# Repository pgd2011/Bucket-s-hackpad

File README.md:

# Bucket's Hackpad: RP2040 Macro Keyboard ⌨️

A custom macro pad project utilizing the Seeed XIAO RP2040 microcontroller for USB input and RGB lighting.

Built as part of [Hack Club](https://hackclub.com)'s Blueprint program.

---

## ✨ Features
*   **Microcontroller:** Seeed XIAO RP2040 (motherboard of the keyboard)
*   **Switches:** MX-Style switches (Note: the project documentation lists 16 components used, despite the description mentioning 6 keys)
*   **Lighting:** SK6812 MINI-E LEDs (RGB lighting for the keyboard)
*   **Design Tools:** Schematic & PCB designed using **KiCad**; Case designed using **Autodesk Fusion**

## 🛠️ Bill of Materials (BOM)
| Item | Quantity | Description |
| :--- | :---: | :--- |
| Seeed XIAO RP2040 | x1 | Main motherboard |
| MX-Style switches | x16 | The keys of the keyboard |
| SK6812 MINI-E LEDs | x2 | RGB lighting |
| M3x16mm screws | x4 | For joining the top and bottom of the case |
| 3D Printed Case | x1 | Custom enclosure |

| Case Enclosure | PCB Layout | Circuit Schematic |
| :---: | :---: | :---: |
|  |  |  |

## 💡 How It Was Made
The project was created by wiring the switches in a matrix and routing the PCB in KiCad. The mechanical enclosure design took some effort to finalize the exact dimensions in Fusion 360.

## 😄 Acknowledgment
*   This project wouldn't have been possible without the documentation from HackClub themselves from https://blueprint.hackclub.com/hackpad
*   My sincere thanks to my elder brother [@P-G-D](https://github.com/P-G-D) for guidance, motivation, and helpful conversations.

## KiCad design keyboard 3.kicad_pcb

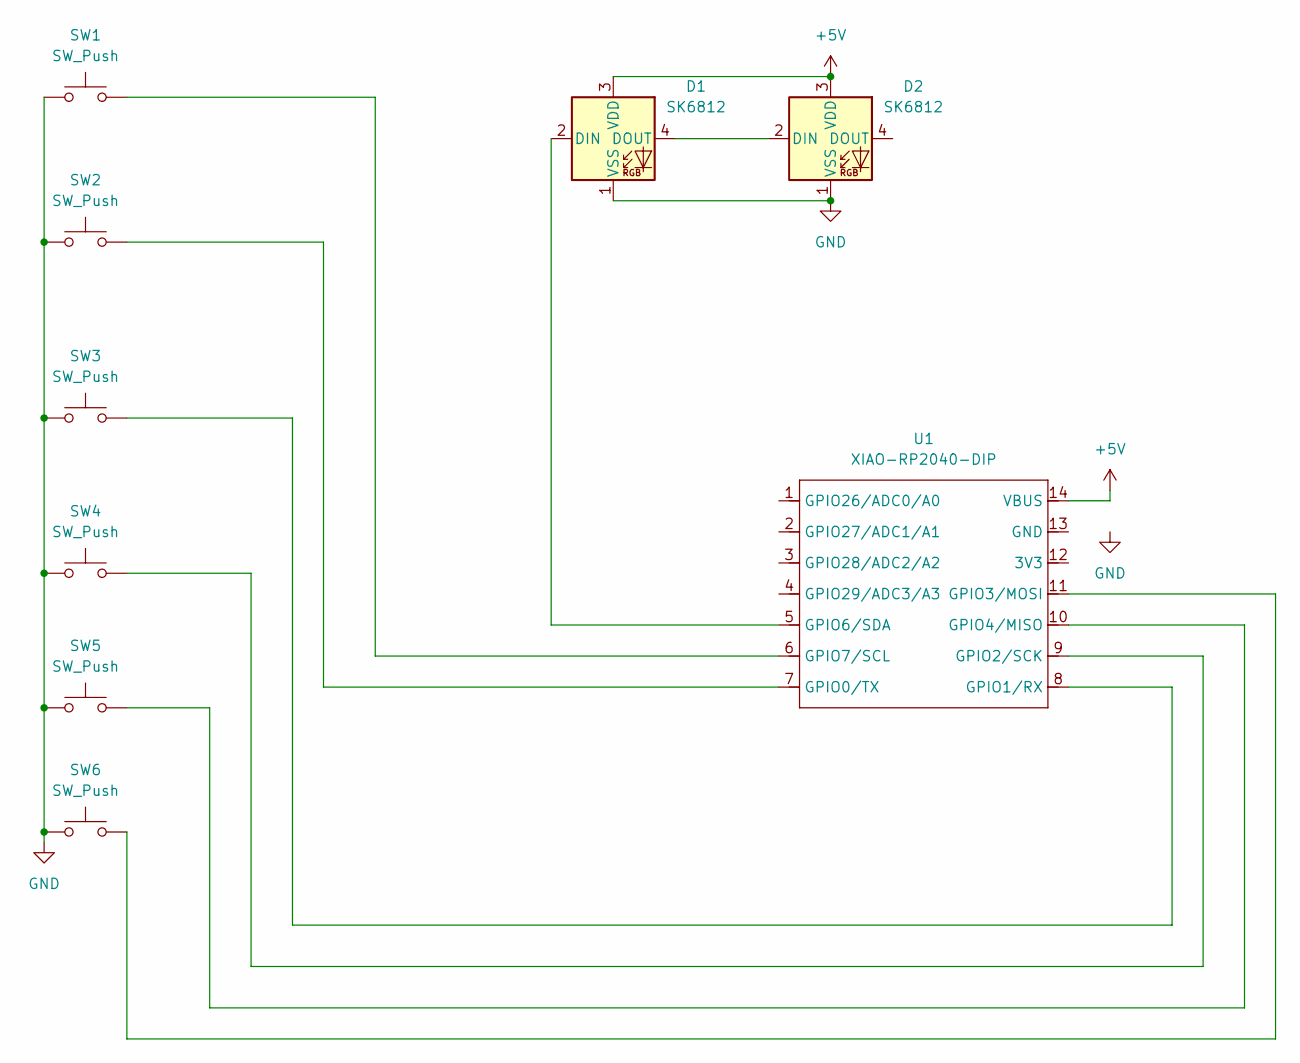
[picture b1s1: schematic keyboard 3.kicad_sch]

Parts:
D1, D2: SK6812; LED_SK6812MINI_PLCC4_3.5x3.5mm_P1.75mm
SW1, SW2, SW3, SW4, SW5, SW6: SW_Push; SW_Cherry_MX_1.00u_PCB
U1: XIAO-RP2040-DIP

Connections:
+5V: D1.3 (VDD), D2.3 (VDD), U1.14 (VBUS)
GND: D1.1 (VSS), D2.1 (VSS), SW1.1, SW2.1, SW3.1, SW4.1, SW5.1, SW6.1
unnamed: D1.2 (DIN), U1.5 (GPIO6/SDA)
unnamed: D1.4 (DOUT), D2.2 (DIN)
unnamed: SW2.2, U1.7 (GPIO0/TX)
unnamed: SW3.2, U1.8 (GPIO1/RX)
unnamed: SW4.2, U1.9 (GPIO2/SCK)
unnamed: SW6.2, U1.11 (GPIO3/MOSI)
unnamed: SW5.2, U1.10 (GPIO4/MISO)
unnamed: SW1.2, U1.6 (GPIO7/SCL)

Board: 2 copper layers, 9 parts (0 on the bottom side), 10 nets, no tracks yet.

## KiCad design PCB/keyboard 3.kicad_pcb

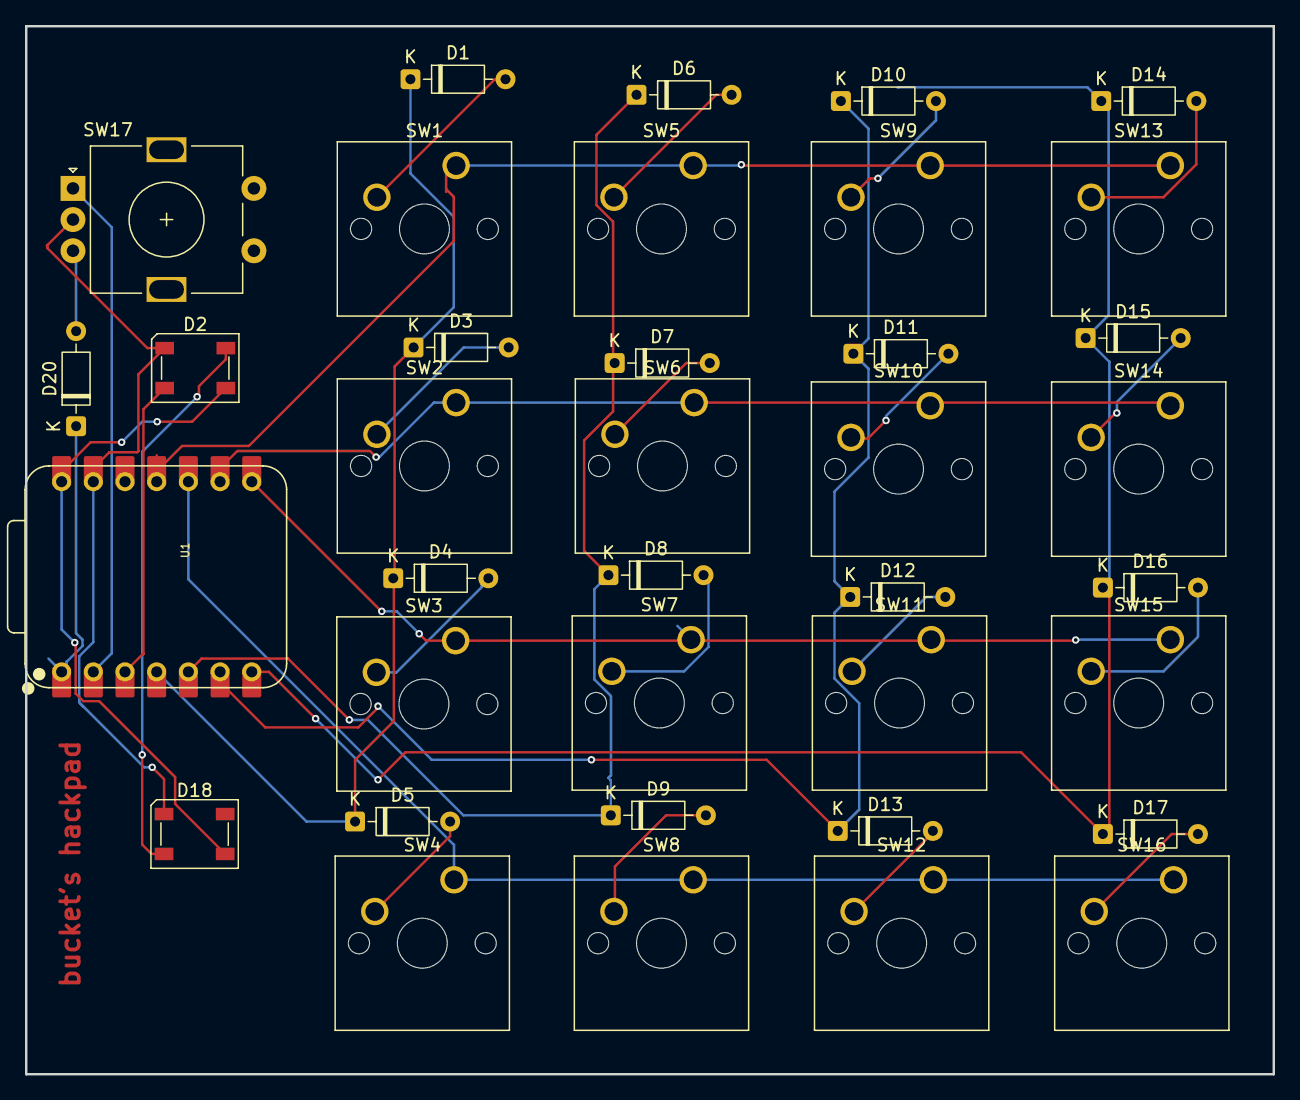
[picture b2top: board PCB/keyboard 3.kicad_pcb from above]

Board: 2 copper layers, 100.0 x 84.0 mm, 37 parts (0 on the bottom side), 31 nets.

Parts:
D1, D3, D4, D5, D6, D7, D8, D9, D10, D11, D12, D13, D14, D15, D16, D17, D20: 1N4148; D_DO-35_SOD27_P7.62mm_Horizontal
D2, D18: SK6812; LED_SK6812_PLCC4_5.0x5.0mm_P3.2mm
SW1, SW2, SW3, SW4, SW5, SW6, SW7, SW8, SW9, SW10, SW11, SW12, SW13, SW14, SW15, SW16: SW_Push; SW_Cherry_MX_1.00u_PCB
SW17: RotaryEncoder; RotaryEncoder_Alps_EC11E-Switch_Vertical_H20mm
U1: XIAO-RP2040-DIP

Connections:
+5V: D2.3 (VDD), D18.3 (VDD), U1.14 (VBUS)
GND: D2.1 (VSS), D18.1 (VSS), SW17.C, U1.13 (GND)
unnamed: D1.2 (A), SW1.2
unnamed: D1.1 (K), D3.1 (K), D4.1 (K), D5.1 (K), U1.4 (GPIO29/ADC3/A3)
unnamed: D2.2 (DIN), U1.3 (GPIO28/ADC2/A2)
unnamed: D3.2 (A), SW2.2
unnamed: D4.2 (A), SW3.2
unnamed: D5.2 (A), SW4.2
unnamed: D6.2 (A), SW5.2
unnamed: D6.1 (K), D7.1 (K), D8.1 (K), D9.1 (K), U1.5 (GPIO6/SDA)
unnamed: D7.2 (A), SW6.2
unnamed: D8.2 (A), SW7.2
unnamed: D9.2 (A), SW8.2
unnamed: D10.2 (A), SW9.2
unnamed: D10.1 (K), D11.1 (K), D12.1 (K), D13.1 (K), U1.6 (GPIO7/SCL)
unnamed: D11.2 (A), SW10.2
unnamed: D12.2 (A), SW11.2
unnamed: D13.2 (A), SW12.2
unnamed: D14.2 (A), SW13.2
unnamed: D14.1 (K), D15.1 (K), D16.1 (K), D17.1 (K), U1.7 (GPIO0/TX)
unnamed: D15.2 (A), SW14.2
unnamed: D16.2 (A), SW15.2
unnamed: D17.2 (A), SW16.2
unnamed: D2.4 (DOUT), D18.2 (DIN)
unnamed: D20.2 (A), SW17.B
unnamed: D20.1 (K), U1.1 (GPIO26/ADC0/A0)
unnamed: SW3.1, SW7.1, SW11.1, SW15.1, U1.8 (GPIO1/RX)
unnamed: SW2.1, SW6.1, SW10.1, SW14.1, U1.9 (GPIO2/SCK)
unnamed: SW1.1, SW5.1, SW9.1, SW13.1, U1.11 (GPIO3/MOSI)
unnamed: SW4.1, SW8.1, SW12.1, SW16.1, U1.10 (GPIO4/MISO)
unnamed: SW17.A, U1.2 (GPIO27/ADC1/A1)

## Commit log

2026-01-16 Rename Keyboard 1.kicad_pro to pro/Keyboard 1.kicad_pro
2026-01-16 Rename Case.png to images/Case.png
2026-01-16 Rename PCB.png to images/PCB.png
2026-01-16 Rename Schematic.png to images/Schematic.png
2026-01-17 Rename Screenshot 2026-01-17 212008.png to images/PCB.png
2026-01-17 Rename Screenshot 2026-01-17 212045.png to images/Case.png
2026-01-17 Create LICENSE
2026-01-19 Rename keyboard 3.kicad_pro to pro/keyboard 3.kicad_pro
2026-01-19 Rename Screenshot 2026-01-19 223656.png to images/Schematic.png
2026-01-19 Rename Screenshot 2026-01-19 223757.png to images/PCB.png
2026-01-19 Rename Screenshot 2026-01-19 223823.png to images/Case.png
2026-01-19 Rename bucket's keyboard.step to case/bucket's keyboard.step
